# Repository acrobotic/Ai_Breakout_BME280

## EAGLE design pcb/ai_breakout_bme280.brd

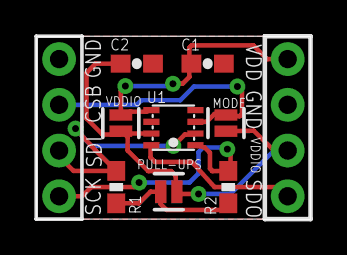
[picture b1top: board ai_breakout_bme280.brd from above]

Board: 2 copper layers, 15.2 x 10.2 mm, 11 parts (1 on the bottom side), 8 nets.

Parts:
C1, C2: CAP-0603
J1: 1X04NOFIRST; 1X04-NOFIRST
J3: 1X04
MODE: 1X02-SJ-NO
PULL-UPS: 1X02-SJ-NO
R1, R2: 4.7K; RES-0603
U1: BME280
U$2: AI-LOGOXS; AI-LOGO-XS
VDDIO: 1X02-SJ-NO

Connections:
CSB: J3.2, MODE.1, U1.2
GND: C1.2, C2.2, J1.3, J3.1, U1.1, U1.7
unnamed: PULL-UPS.1, R1.2, R2.2
SCK: J3.4, R2.1, U1.4
SDI: J3.3, R1.1, U1.3
SDO: J1.1, U1.5
VDD: C1.1, J1.4, U1.8, VDDIO.1
VDDIO: C2.1, J1.2, MODE.2, PULL-UPS.2, U1.6, VDDIO.2

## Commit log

2015-06-29 changes and renaming
2015-06-29 renaming
